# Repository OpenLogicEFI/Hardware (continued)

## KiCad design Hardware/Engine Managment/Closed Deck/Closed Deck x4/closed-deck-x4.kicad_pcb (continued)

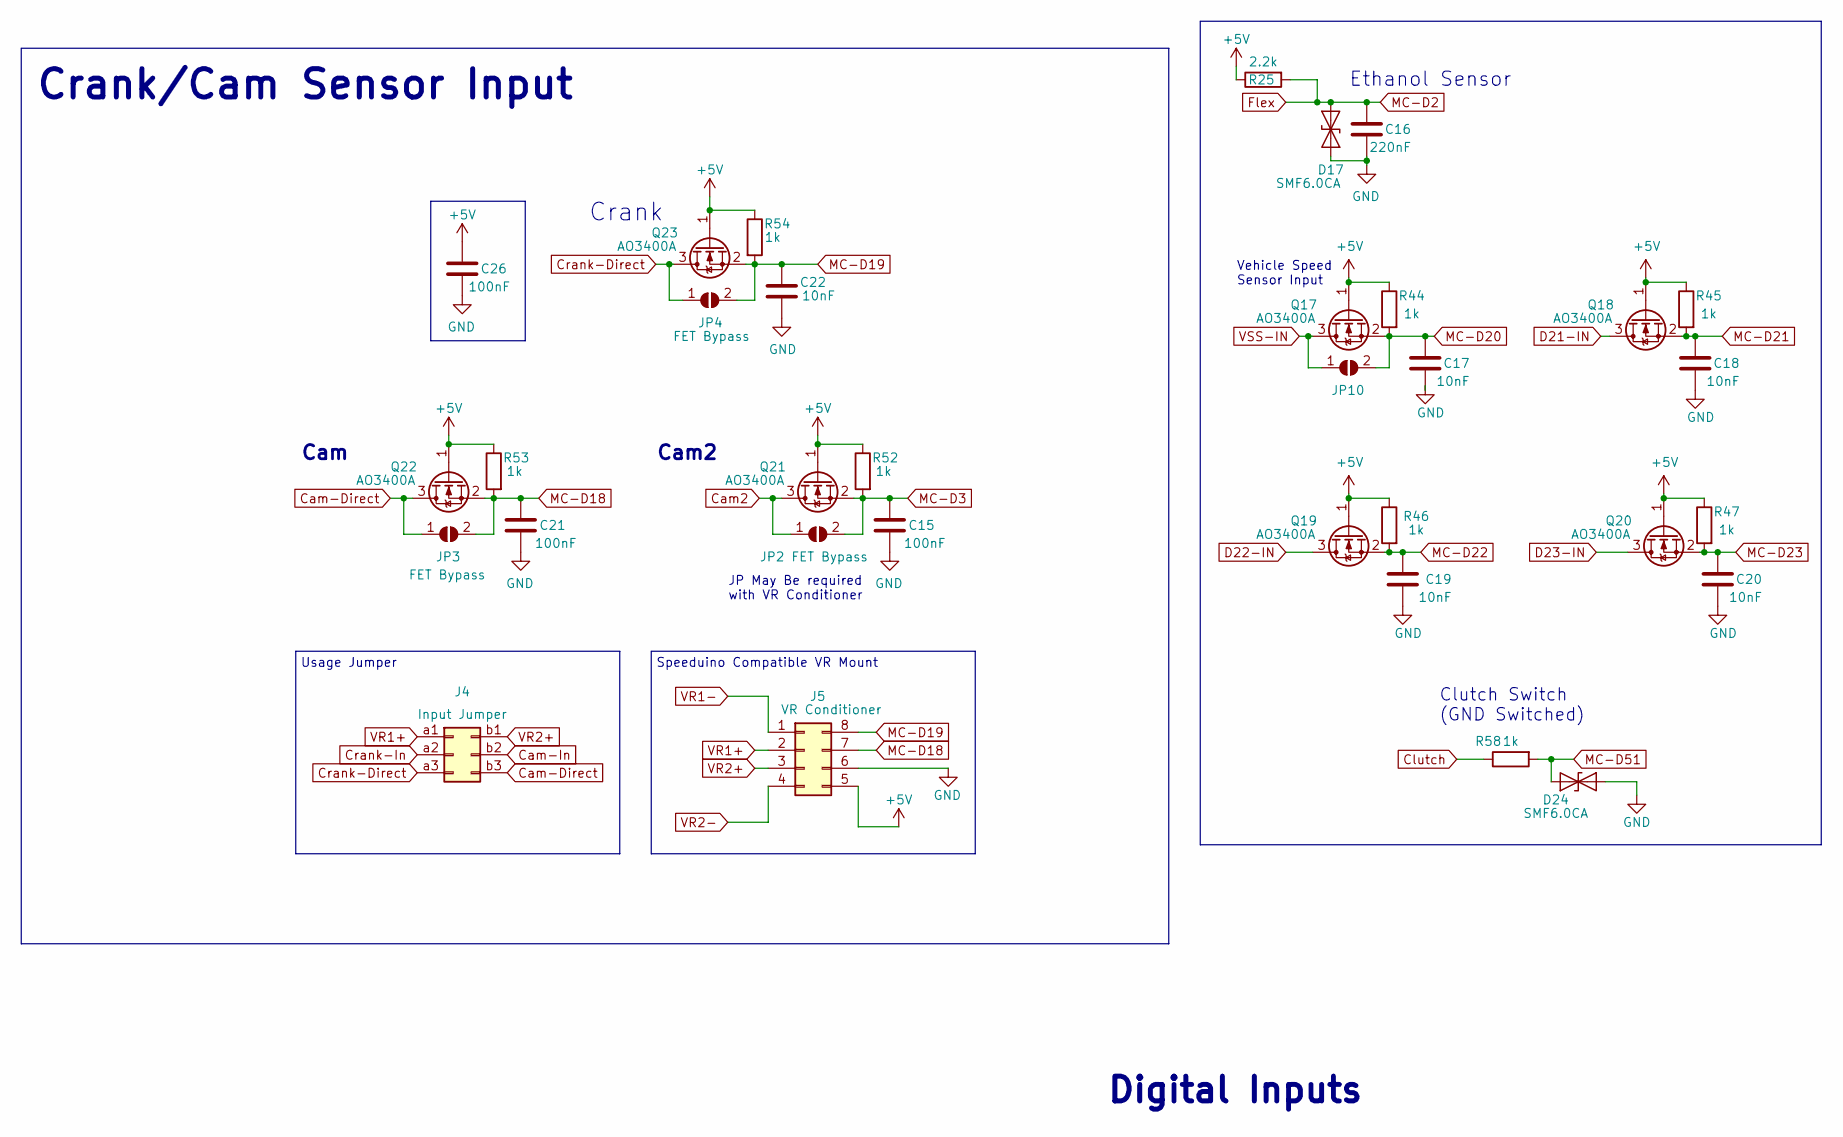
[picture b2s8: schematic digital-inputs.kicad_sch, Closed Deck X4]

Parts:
C15, C21, C26: 100nF; C_0402_1005Metric; LCSC C307331
C16: 220nF; C_0402_1005Metric; LCSC C16772
C17, C18, C19, C20, C22: 10nF; C_0402_1005Metric; LCSC C15195
D17, D24: SMF6.0CA; D_SOD-123F; LCSC C2990473
J4: Input Jumper; PinHeader2x03_Jumper
J5: VR Conditioner; Socket_VRConditioner_Corrected
JP2, JP3, JP4, JP10: FET Bypass; SolderJumper-2_P1.3mm_Open_RoundedPad1.0x1.5mm
Q17, Q18, Q19, Q20, Q21, Q22, Q23: AO3400A; SOT-23
R25: 2.2k; R_0402_1005Metric; Manufacture Part Number 0402WGF2201TCE; LCSC C25879
R44, R45, R46, R47, R52, R53, R54, R58: 1k; R_0402_1005Metric; Manufacture Part Number 0402WGF1001TCE; LCSC C11702

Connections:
+5V: C26.2, J5.5, Q17.1 (G), Q18.1 (G), Q19.1 (G), Q20.1 (G), Q21.1 (G), Q22.1 (G), Q23.1 (G), R25.1, R44.1, R45.1, R46.1, R47.1, R52.1, R53.1, R54.1; also elsewhere on the board
Cam2: JP2.1 (A), Q21.3 (D); also elsewhere on the board
Cam-Direct: J4.b3, JP3.1 (A), Q22.3 (D)
Cam-In: J4.b2; also elsewhere on the board
Clutch: R58.1; also elsewhere on the board
Crank-Direct: J4.a3, JP4.1 (A), Q23.3 (D)
Crank-In: J4.a2; also elsewhere on the board
D21-IN: Q18.3 (D); also elsewhere on the board
D22-IN: Q19.3 (D); also elsewhere on the board
D23-IN: Q20.3 (D); also elsewhere on the board
Flex: C16.1, D17.1 (A1), R25.2; also elsewhere on the board
GND: C15.1, C16.2, C17.2, C18.2, C19.2, C20.2, C21.1, C22.1, C26.1, D17.2 (A2), D24.1 (A1), J5.6; also elsewhere on the board
MC-D3: C15.2, JP2.2 (B), Q21.2 (S), R52.2; also elsewhere on the board
MC-D18: C21.2, J5.7, JP3.2 (B), Q22.2 (S), R53.2; also elsewhere on the board
MC-D19: C22.2, J5.8, JP4.2 (B), Q23.2 (S), R54.2; also elsewhere on the board
MC-D20: C17.1, JP10.2 (B), Q17.2 (S), R44.2; also elsewhere on the board
MC-D21: C18.1, Q18.2 (S), R45.2; also elsewhere on the board
MC-D22: C19.1, Q19.2 (S), R46.2; also elsewhere on the board
MC-D23: C20.1, Q20.2 (S), R47.2; also elsewhere on the board
MC-D51: D24.2 (A2), R58.2; also elsewhere on the board
VR1+: J4.a1, J5.2
VR1-: J5.1; also elsewhere on the board
VR2+: J4.b1, J5.3
VR2-: J5.4; also elsewhere on the board
VSS-IN: JP10.1 (A), Q17.3 (D); also elsewhere on the board

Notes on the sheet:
Vehicle Speed Sensor Input
JP May Be required with VR Conditioner
Cam
Speeduino Compatible VR Mount
Clutch Switch (GND Switched)
Ethanol Sensor
Usage Jumper
Crank
Crank/Cam Sensor Input
Cam2
Digital Inputs

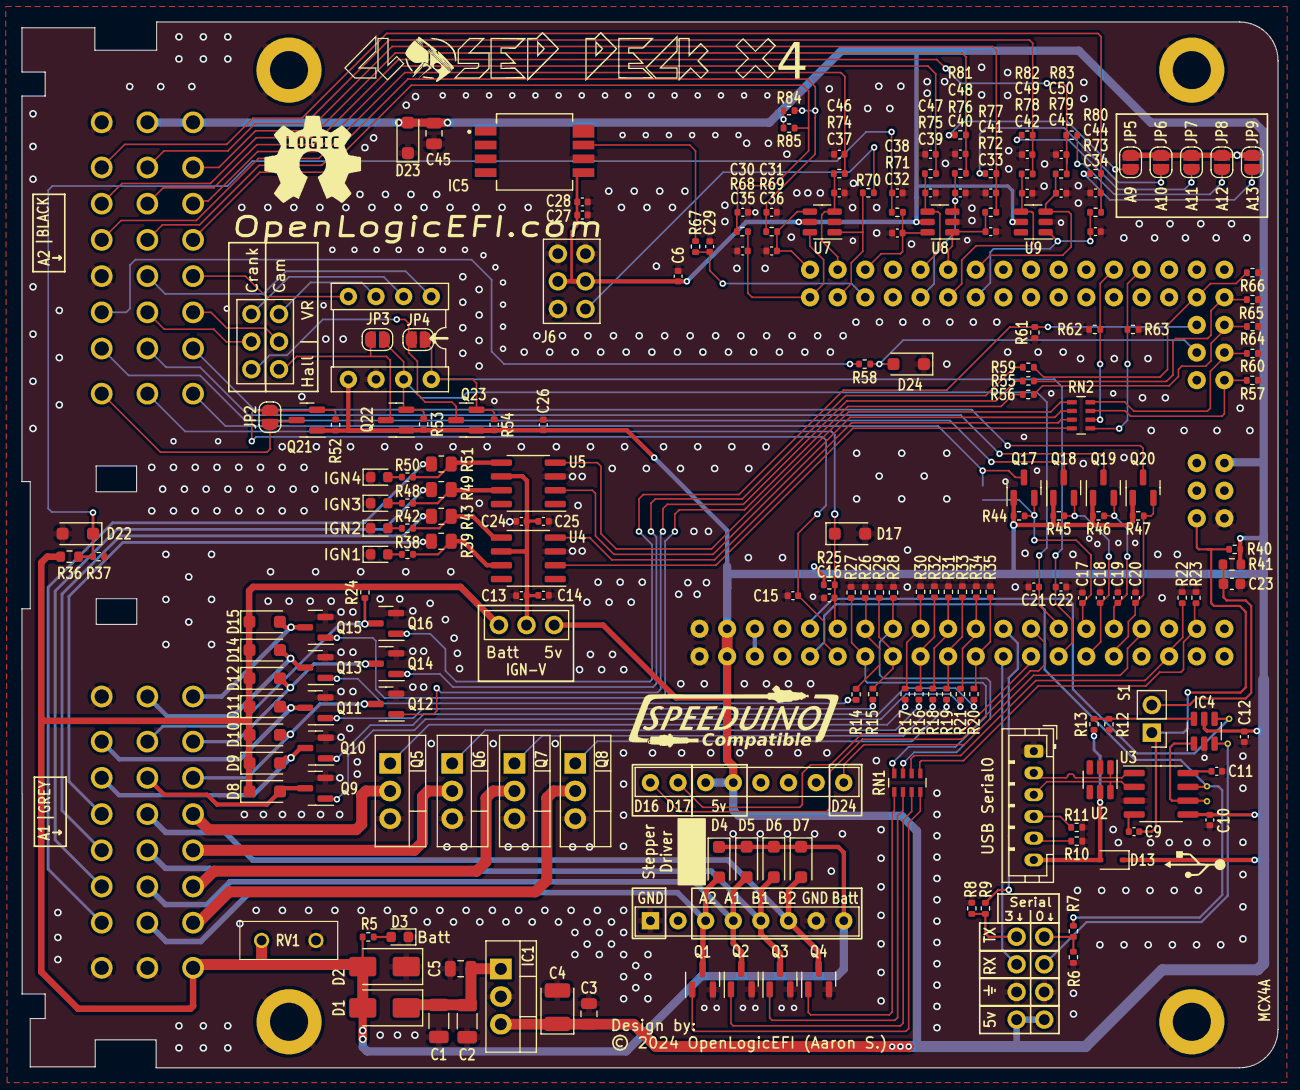
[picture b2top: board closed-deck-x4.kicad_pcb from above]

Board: 2 copper layers, 115.5 x 96.2 mm, 216 parts (1 on the bottom side), 147 nets.

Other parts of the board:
U6: MEGA_PRO_EMBED_CH340G_{slash}_ATMEGA2560; Arduino_Mega_Mini_2560_SmallCrtYd_NoVin

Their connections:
+3.3V: U6.3V3_1 (3V3), U6.3V3_2 (3V3)
+5V: U6.5V_1 (5V), U6.5V_2 (5V), U6.5V_3 (5V); also elsewhere on the board
Flex: U6.D2; also elsewhere on the board
GND: U6.GND_1 (GND), U6.GND_2 (GND), U6.GND_3 (GND); also elsewhere on the board
MC-A0: U6.A0; also elsewhere on the board
MC-A1: U6.A1; also elsewhere on the board
MC-A2: U6.A2; also elsewhere on the board
MC-A3: U6.A3; also elsewhere on the board
MC-A4: U6.A4; also elsewhere on the board
MC-A5: U6.A5; also elsewhere on the board
MC-A8: U6.A8; also elsewhere on the board
MC-A9: U6.A9; also elsewhere on the board
MC-A10: U6.A10; also elsewhere on the board
MC-A11: U6.A11; also elsewhere on the board
MC-A12: U6.A12; also elsewhere on the board
MC-A13: U6.A13; also elsewhere on the board
MC-D0-RX0: U6.RX; also elsewhere on the board
MC-D1-TX0: U6.TX; also elsewhere on the board
MC-D3: U6.D3; also elsewhere on the board
MC-D4: U6.D4; also elsewhere on the board
MC-D5: U6.D5; also elsewhere on the board
MC-D6: U6.D6; also elsewhere on the board
MC-D7: U6.D7; also elsewhere on the board
MC-D8: U6.D8; also elsewhere on the board
MC-D9: U6.D9; also elsewhere on the board
MC-D10: U6.D10; also elsewhere on the board
MC-D11: U6.D11; also elsewhere on the board
MC-D12: U6.D12; also elsewhere on the board
MC-D13: U6.D13; also elsewhere on the board
MC-D14-TX3: U6.D14; also elsewhere on the board
MC-D15-RX3: U6.D15; also elsewhere on the board
MC-D16: U6.D16; also elsewhere on the board
MC-D17: U6.D17; also elsewhere on the board
MC-D18: U6.D18; also elsewhere on the board
MC-D19: U6.D19; also elsewhere on the board
MC-D20: U6.D20; also elsewhere on the board
MC-D21: U6.D21; also elsewhere on the board
MC-D22: U6.D22; also elsewhere on the board
MC-D23: U6.D23; also elsewhere on the board
MC-D24: U6.D24; also elsewhere on the board
MC-D27: U6.D27; also elsewhere on the board
MC-D28: U6.D28; also elsewhere on the board
MC-D38: U6.D38; also elsewhere on the board
MC-D40: U6.D40; also elsewhere on the board
MC-D45: U6.D45; also elsewhere on the board
MC-D47: U6.D47; also elsewhere on the board
MC-D48: U6.D48; also elsewhere on the board
MC-D49: U6.D49; also elsewhere on the board
MC-D50: U6.D50; also elsewhere on the board
MC-D51: U6.D51; also elsewhere on the board
MC-D52: U6.D52; also elsewhere on the board
MC-RESET: U6.RESET; also elsewhere on the board

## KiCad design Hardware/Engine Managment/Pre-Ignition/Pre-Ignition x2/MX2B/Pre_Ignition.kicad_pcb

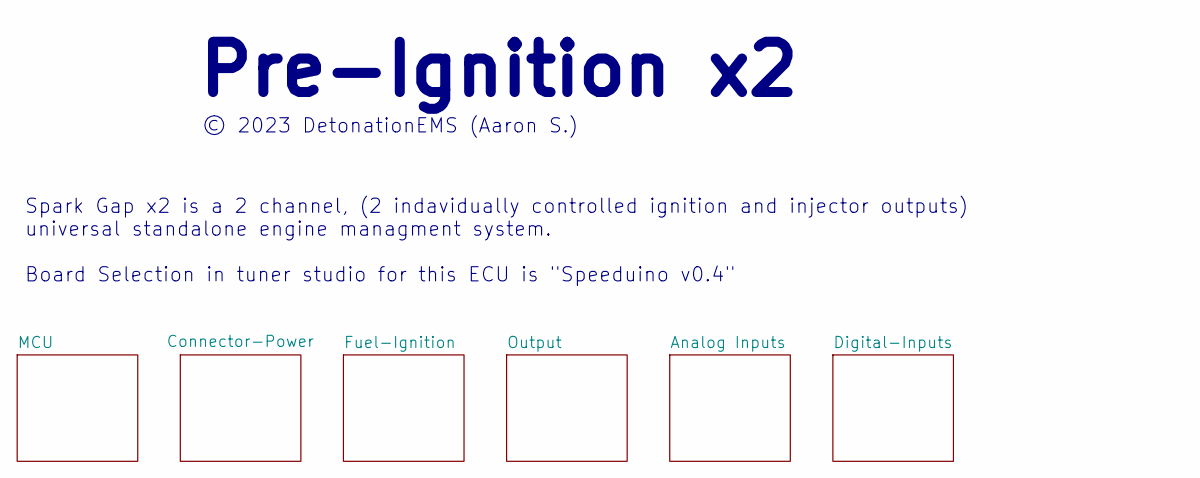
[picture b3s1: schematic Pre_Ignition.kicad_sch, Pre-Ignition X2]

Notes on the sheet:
Pre-Ignition x2
Spark Gap x2 is a 2 channel, (2 indavidually controlled ignition and injector outputs) universal standalone engine managment system. Board Selection in tuner studio for this ECU is "Speeduino v0.4"
© 2023 DetonationEMS (Aaron S.)

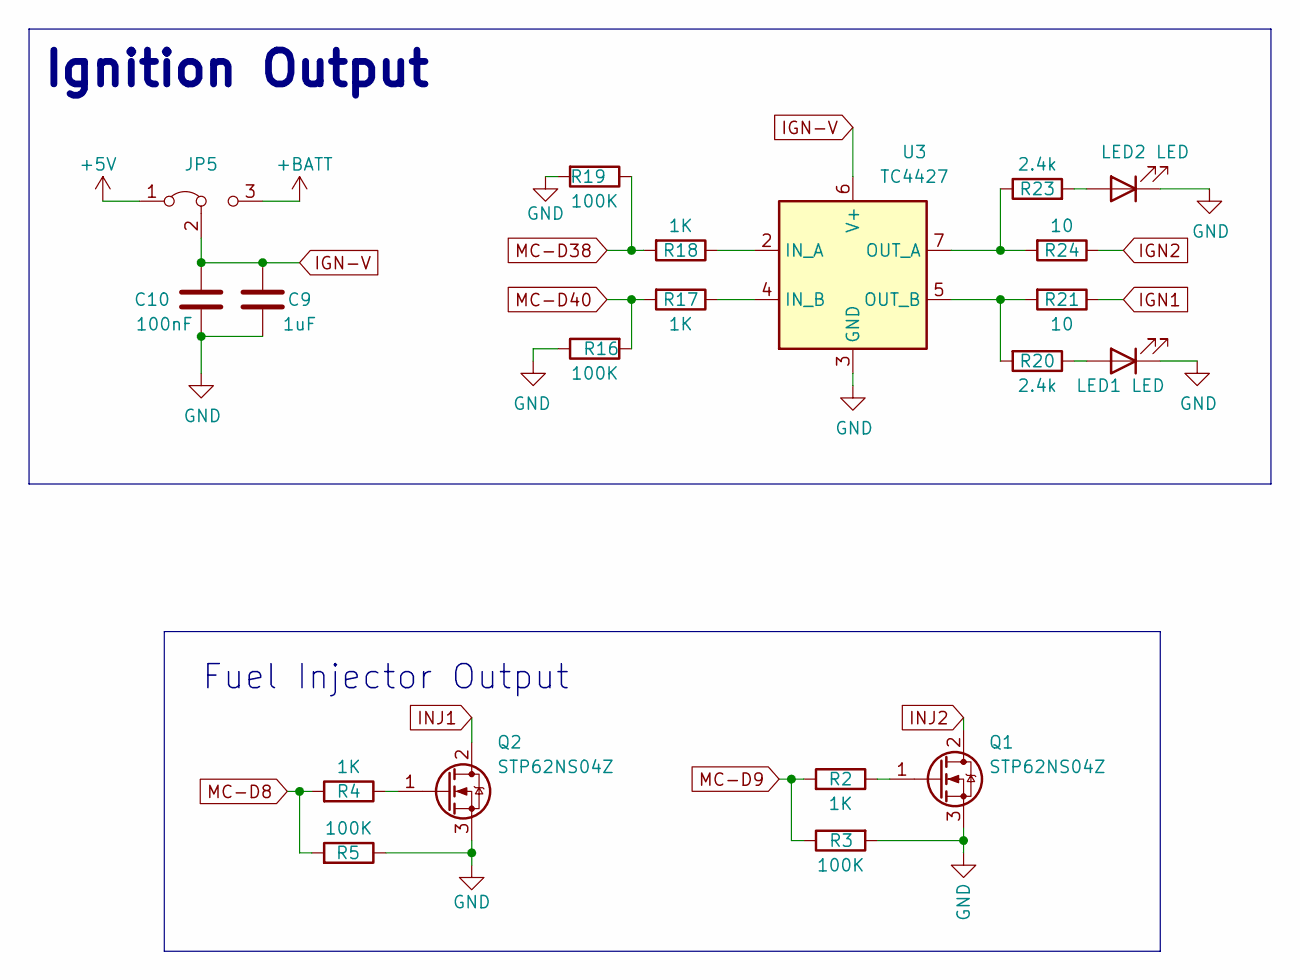
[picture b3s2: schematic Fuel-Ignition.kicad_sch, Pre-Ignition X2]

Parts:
C9: 1uF; C_0603_1608Metric; LCSC C15849
C10: 100nF; C_0603_1608Metric; LCSC C14663
JP5: Jumper_3_Bridged12; SolderJumper-3_P1.3mm_Bridged12_RoundedPad1.0x1.5mm_NumberL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
LED1, LED2: LED; LED_0603_1608Metric; LCSC C2286
Q1: STP62NS04Z; TO-220-3_Vertical; Manufacturer_Part_Number STP62NS04Z; Mouser Part Number 511-STP62NS04Z
Q2: STP62NS04Z; TO-220-3_Vertical; Manufacturer_Part_Number STP62NS04Z
R2, R4, R17, R18: 1K; R_0603_1608Metric; LCSC C21190
R3, R5, R16, R19: 100K; R_0603_1608Metric; LCSC C25803
R20, R23: 2.4k; R_0603_1608Metric; LCSC C22940
R21, R24: 10; R_1206_3216Metric; LCSC C17903
U3: TC4427; SOIC-8_3.9x4.9mm_P1.27mm; LCSC C31450

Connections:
+BATT: JP5.3 (B); also elsewhere on the board
IGN1: R21.1; also elsewhere on the board
IGN2: R24.1; also elsewhere on the board
IGN-V: C9.1, C10.1, JP5.2 (C), U3.6 (V+)
INJ1: Q2.2 (D); also elsewhere on the board
INJ2: Q1.2 (D); also elsewhere on the board
MC-D8: R4.2, R5.2; also elsewhere on the board
MC-D9: R2.2, R3.1; also elsewhere on the board
MC-D38: R18.2, R19.1; also elsewhere on the board
MC-D40: R16.2, R17.2; also elsewhere on the board
unnamed: LED1.2 (A), R20.1
unnamed: LED2.2 (A), R23.2
unnamed: Q1.1 (G), R2.1
unnamed: Q2.1 (G), R4.1
unnamed: R18.1, U3.2 (IN_A)
unnamed: R17.1, U3.4 (IN_B)
unnamed: R23.1, R24.2, U3.7 (OUT_A)
unnamed: R20.2, R21.2, U3.5 (OUT_B)

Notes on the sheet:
Ignition Output
Fuel Injector Output

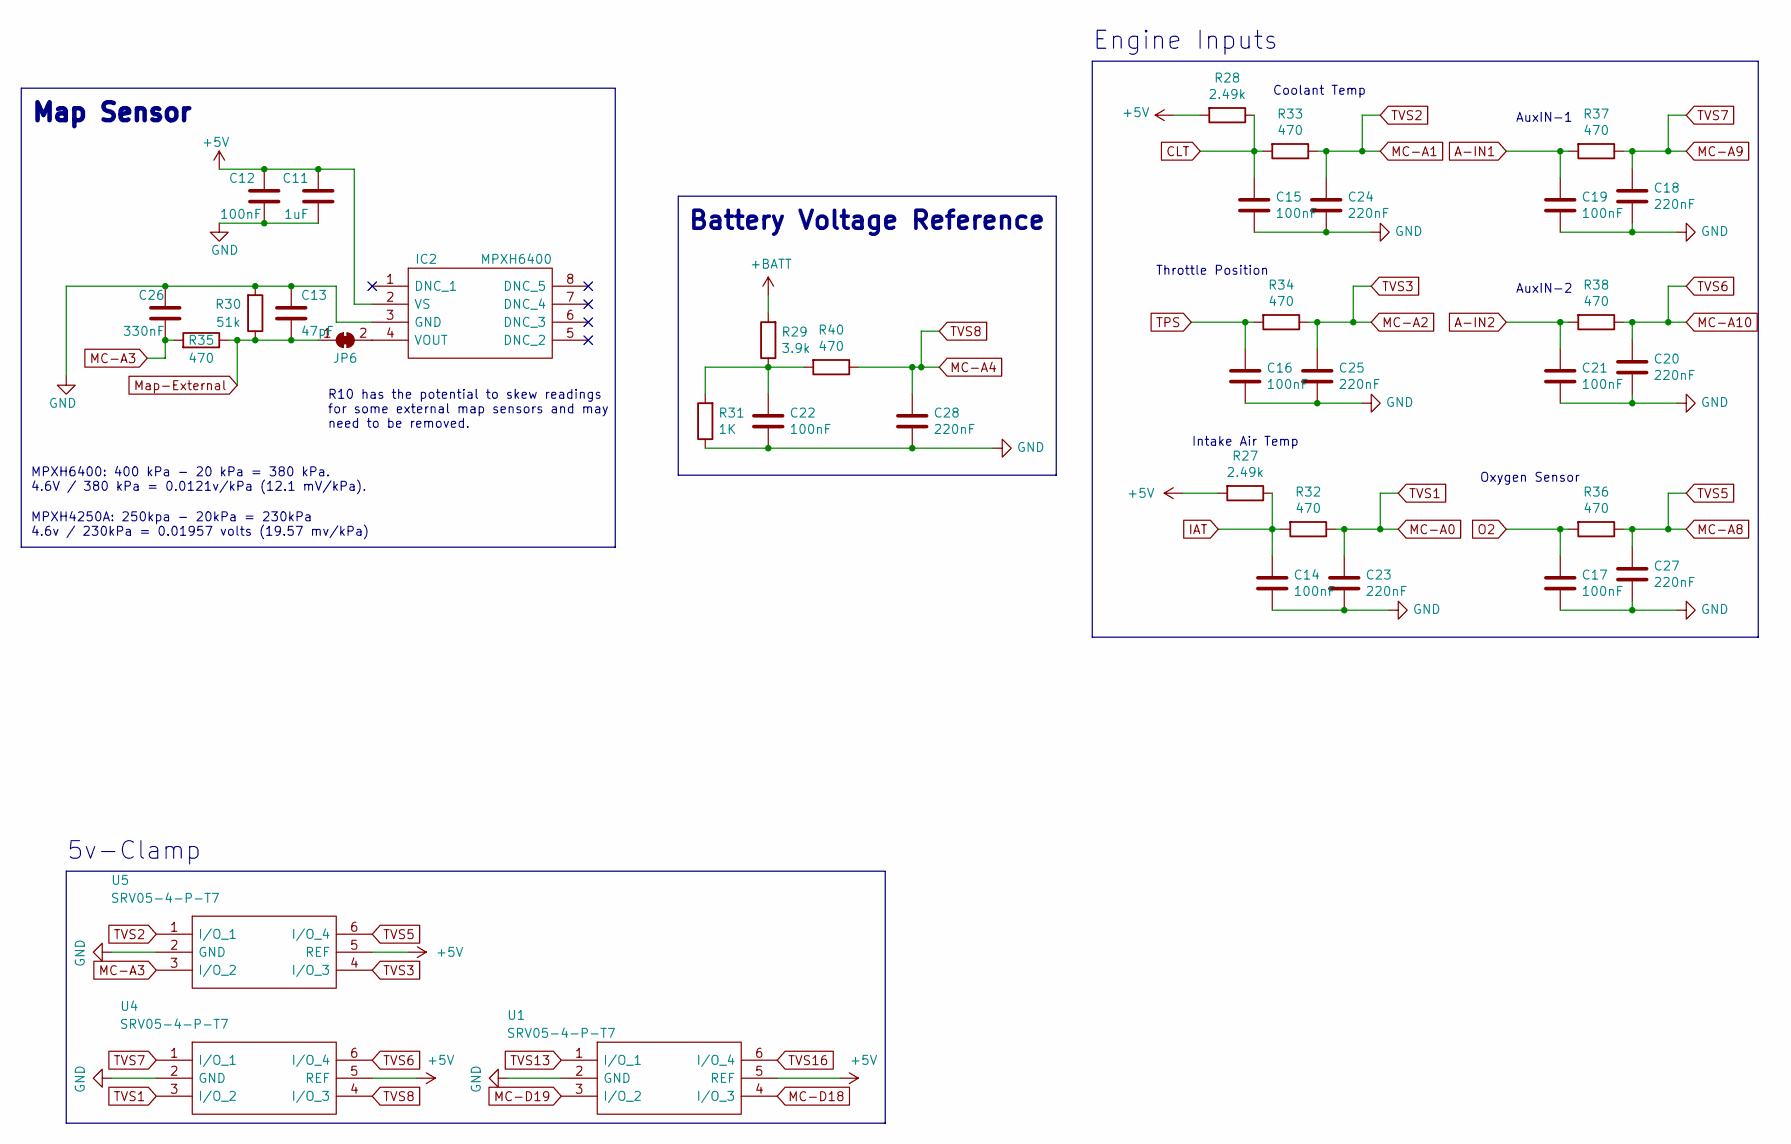
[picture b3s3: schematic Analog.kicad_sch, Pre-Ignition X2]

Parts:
C11: 1uF; C_0603_1608Metric; LCSC C15849
C12, C14, C15, C16, C17, C19, C21, C22: 100nF; C_0603_1608Metric; LCSC C14663
C13: 47pF; C_0603_1608Metric; LCSC C1671
C18, C20, C23, C24, C25, C27, C28: 220nF; C_0603_1608Metric; LCSC C5378
C26: 330nF; C_0603_1608Metric; LCSC C1615
IC2: MPXH6400; MPXH6250; Manufacturer_Part_Number MPXH6250AC6U; Mouser Part Number 841-MPXH6250AC6U
JP6: SolderJumper-2_P1.3mm_Bridged_RoundedPad1.0x1.5mm
R27, R28: 2.49k; R_0603_1608Metric; LCSC C309658
R29: 3.9k; R_0603_1608Metric; LCSC C23018
R30: 51k; R_0603_1608Metric; LCSC C23196
R31: 1K; R_0603_1608Metric; LCSC C21190
R32, R33, R34, R35, R36, R37, R38, R40: 470; R_0603_1608Metric; LCSC C23179
U1, U4, U5: SRV05-4-P-T7; SOT-23-6; LCSC C85364

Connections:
+BATT: R29.2; also elsewhere on the board
A-IN1: C19.1, R37.2; also elsewhere on the board
A-IN2: C21.1, R38.2; also elsewhere on the board
CLT: C15.1, R28.1, R33.2; also elsewhere on the board
IAT: C14.1, R27.1, R32.2; also elsewhere on the board
MC-A0: C23.1, R32.1, U4.3 (I/O_2); also elsewhere on the board
MC-A1: C24.1, R33.1, U5.1 (I/O_1); also elsewhere on the board
MC-A3: C26.2, R35.2, U5.3 (I/O_2); also elsewhere on the board
MC-A4: C28.1, R40.1, U4.4 (I/O_3); also elsewhere on the board
MC-A8: C27.1, R36.1, U5.6 (I/O_4); also elsewhere on the board
MC-A9: C18.1, R37.1, U4.1 (I/O_1); also elsewhere on the board
MC-A10: C20.1, R38.1, U4.6 (I/O_4); also elsewhere on the board
MC-D18: U1.4 (I/O_3); also elsewhere on the board
Map-External: C13.1, JP6.1 (A), R30.1, R35.1; also elsewhere on the board
unnamed: C22.1, R29.1, R31.2, R40.2
unnamed: IC2.4 (VOUT), JP6.2 (B)
O2: C17.1, R36.2; also elsewhere on the board
TPS: C16.1, R34.2; also elsewhere on the board
TVS13: U1.1 (I/O_1)
TVS16: U1.6 (I/O_4)

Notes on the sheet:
R10 has the potential to skew readings for some external map sensors and may need to be removed.
5v-Clamp
Coolant Temp
Oxygen Sensor
Engine Inputs
AuxIN-2
Battery Voltage Reference
Map Sensor
MPXH4250A: 250kpa - 20kPa = 230kPa 4.6v / 230kPa = 0.01957 volts (19.57 mv/kPa)
MPXH6400: 400 kPa - 20 kPa = 380 kPa. 4.6V / 380 kPa = 0.0121v/kPa (12.1 mV/kPa).
Intake Air Temp
Throttle Position
AuxIN-1

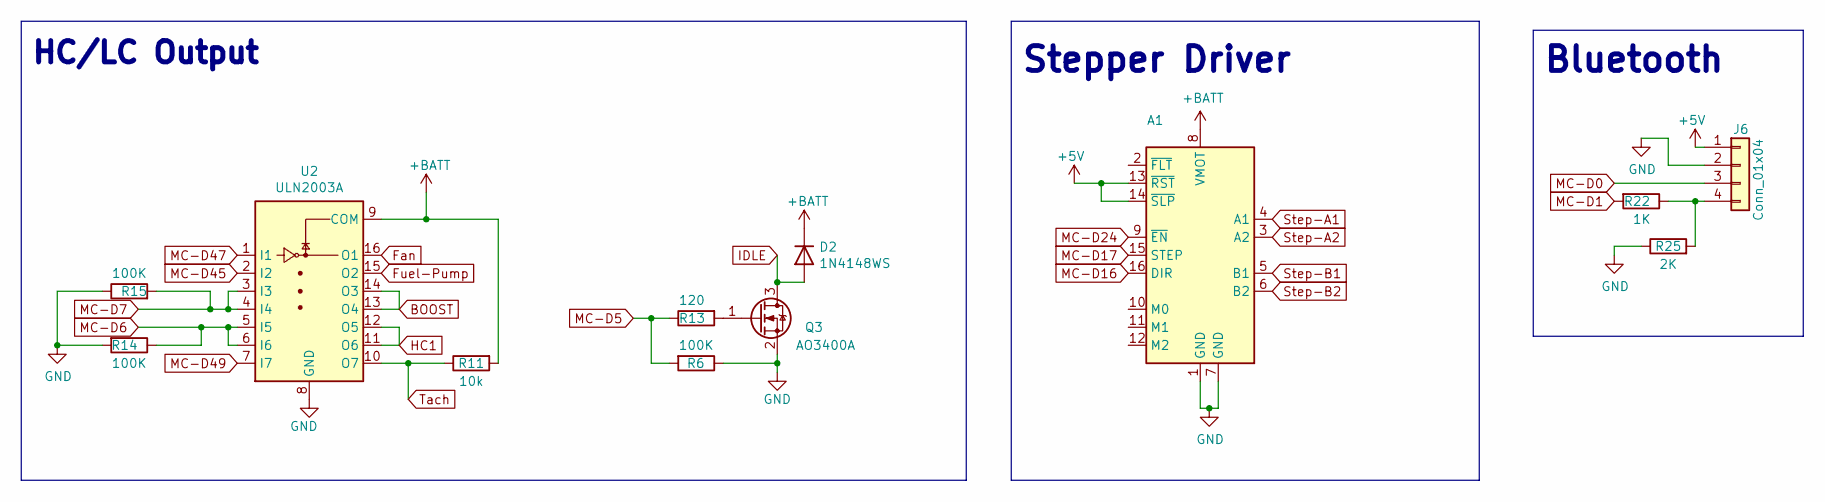
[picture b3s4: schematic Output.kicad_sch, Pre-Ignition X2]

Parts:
A1: Pololu_Breakout_DRV8825; DVR8825-Labeled-Front
D2: 1N4148WS; D_SOD-323F; LCSC C2128
J6: Conn_01x04; 1X4-PROTO
Q3: AO3400A; SOT-23; LCSC C20917
R6, R14, R15: 100K; R_0603_1608Metric; LCSC C25803
R11: 10k; R_0603_1608Metric; LCSC C25804
R13: 120; R_0603_1608Metric; LCSC C22787
R22: 1K; R_0603_1608Metric; LCSC C21190
R25: 2K; R_0603_1608Metric; LCSC C22975
U2: ULN2003A; SOIC-16_3.9x9.9mm_P1.27mm; LCSC C7512

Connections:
+BATT: A1.8 (VMOT), D2.1 (K), R11.2, U2.9 (COM); also elsewhere on the board
BOOST: U2.13 (O4), U2.14 (O3); also elsewhere on the board
Fan: U2.16 (O1); also elsewhere on the board
Fuel-Pump: U2.15 (O2); also elsewhere on the board
HC1: U2.11 (O6), U2.12 (O5); also elsewhere on the board
IDLE: D2.2 (A), Q3.3 (D); also elsewhere on the board
MC-D0: J6.3; also elsewhere on the board
MC-D1: R22.2; also elsewhere on the board
MC-D5: R6.2, R13.1; also elsewhere on the board
MC-D6: R14.1, U2.5 (I5), U2.6 (I6); also elsewhere on the board
MC-D7: R15.2, U2.3 (I3), U2.4 (I4); also elsewhere on the board
MC-D16: A1.16 (DIR); also elsewhere on the board
MC-D17: A1.15 (STEP); also elsewhere on the board
MC-D24: A1.9 (~EN); also elsewhere on the board
MC-D45: U2.2 (I2); also elsewhere on the board
MC-D47: U2.1 (I1); also elsewhere on the board
MC-D49: U2.7 (I7); also elsewhere on the board
unnamed: J6.4, R22.1, R25.2
unnamed: Q3.1 (G), R13.2
Step-A1: A1.4 (A1); also elsewhere on the board
Step-A2: A1.3 (A2); also elsewhere on the board
Step-B1: A1.5 (B1); also elsewhere on the board
Step-B2: A1.6 (B2); also elsewhere on the board
Tach: R11.1, U2.10 (O7); also elsewhere on the board

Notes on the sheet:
Bluetooth
Stepper Driver
HC/LC Output

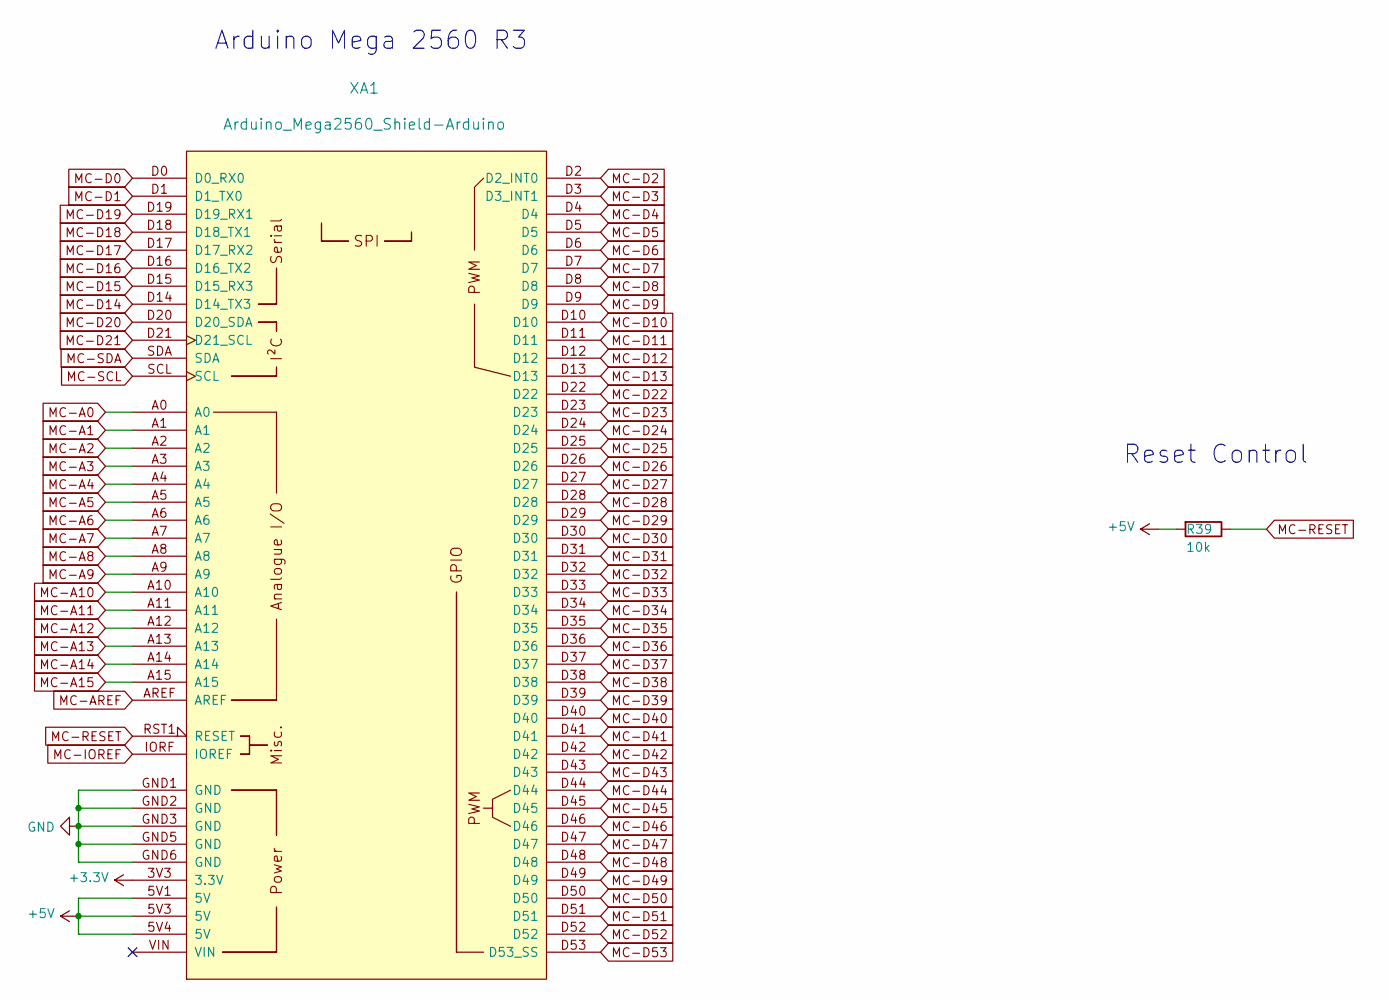
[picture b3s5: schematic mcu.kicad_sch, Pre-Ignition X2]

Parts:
R39: 10k; R_0603_1608Metric; LCSC C25804
XA1: Arduino_Mega2560_Shield-Arduino; Arduino_Mega2560_Shield_IO_Only_No_Silk_Screen

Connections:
+3V3: XA1.3V3 (3.3V)
Flex: XA1.D2 (D2_INT0); also elsewhere on the board
MC-A0: XA1.A0; also elsewhere on the board
MC-A1: XA1.A1; also elsewhere on the board
MC-A3: XA1.A3; also elsewhere on the board
MC-A4: XA1.A4; also elsewhere on the board
MC-A5: XA1.A5
MC-A6: XA1.A6
MC-A7: XA1.A7
MC-A8: XA1.A8; also elsewhere on the board
MC-A9: XA1.A9; also elsewhere on the board
MC-A10: XA1.A10; also elsewhere on the board
MC-A11: XA1.A11
MC-A12: XA1.A12
MC-A13: XA1.A13
MC-A14: XA1.A14
MC-A15: XA1.A15
MC-AREF: XA1.AREF
MC-D0: XA1.D0 (D0_RX0); also elsewhere on the board
MC-D1: XA1.D1 (D1_TX0); also elsewhere on the board
MC-D3: XA1.D3 (D3_INT1)
MC-D4: XA1.D4
MC-D5: XA1.D5; also elsewhere on the board
MC-D6: XA1.D6; also elsewhere on the board
MC-D7: XA1.D7; also elsewhere on the board
MC-D8: XA1.D8; also elsewhere on the board
MC-D9: XA1.D9; also elsewhere on the board
MC-D10: XA1.D10
MC-D11: XA1.D11
MC-D12: XA1.D12
MC-D13: XA1.D13
MC-D14: XA1.D14 (D14_TX3)
MC-D15: XA1.D15 (D15_RX3)
MC-D16: XA1.D16 (D16_TX2); also elsewhere on the board
MC-D17: XA1.D17 (D17_RX2); also elsewhere on the board
MC-D18: XA1.D18 (D18_TX1); also elsewhere on the board
MC-D20: XA1.D20 (D20_SDA); also elsewhere on the board
MC-D21: XA1.D21 (D21_SCL)
MC-D22: XA1.D22
MC-D23: XA1.D23
MC-D24: XA1.D24; also elsewhere on the board
MC-D25: XA1.D25
MC-D26: XA1.D26
MC-D27: XA1.D27
MC-D28: XA1.D28
MC-D29: XA1.D29
MC-D30: XA1.D30
MC-D31: XA1.D31
MC-D32: XA1.D32
MC-D33: XA1.D33
MC-D34: XA1.D34
MC-D35: XA1.D35
MC-D36: XA1.D36
MC-D37: XA1.D37
MC-D38: XA1.D38; also elsewhere on the board
MC-D39: XA1.D39
MC-D40: XA1.D40; also elsewhere on the board
MC-D41: XA1.D41
MC-D42: XA1.D42
MC-D43: XA1.D43
MC-D44: XA1.D44
MC-D45: XA1.D45; also elsewhere on the board
MC-D46: XA1.D46
MC-D47: XA1.D47; also elsewhere on the board
MC-D48: XA1.D48
MC-D49: XA1.D49; also elsewhere on the board
MC-D50: XA1.D50
MC-D51: XA1.D51; also elsewhere on the board
MC-D52: XA1.D52
MC-D53: XA1.D53 (D53_SS)
MC-IOREF: XA1.IORF (IOREF)
MC-RESET: R39.1, XA1.RST1 (RESET)
MC-SCL: XA1.SCL
MC-SDA: XA1.SDA

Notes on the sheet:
Arduino Mega 2560 R3
Reset Control

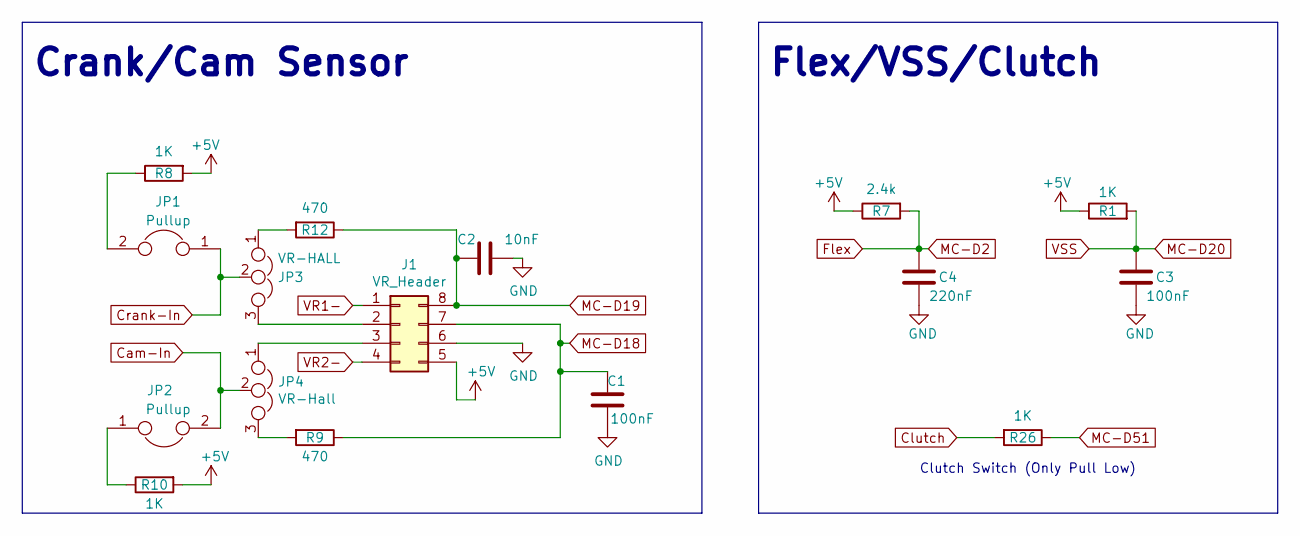
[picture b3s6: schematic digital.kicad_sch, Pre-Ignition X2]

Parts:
C1, C3: 100nF; C_0603_1608Metric; LCSC C14663
C2: 10nF; C_0603_1608Metric; LCSC C57112
C4: 220nF; C_0603_1608Metric; LCSC C5378
J1: VR_Header; DIP-8_W7.62mm_Socket_VRConditioner
JP1, JP2: Pullup; 1x02-Proto
JP3: VR-HALL; 3x1-GPIO
JP4: VR-Hall; 3x1-GPIO
R1, R8, R10, R26: 1K; R_0603_1608Metric; LCSC C21190
R7: 2.4k; R_0603_1608Metric; LCSC C22940
R9, R12: 470; R_0603_1608Metric; LCSC C23179

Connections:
Cam-In: JP2.2, JP4.2; also elsewhere on the board
Clutch: R26.2; also elsewhere on the board
Crank-In: JP1.1, JP3.2; also elsewhere on the board
Flex: C4.1, R7.2; also elsewhere on the board
MC-D18: C1.2, J1.7, R9.1; also elsewhere on the board
MC-D20: C3.1, R1.2; also elsewhere on the board
MC-D51: R26.1; also elsewhere on the board
unnamed: J1.2, JP3.3
unnamed: J1.3, JP4.1
unnamed: JP1.2, R8.1
unnamed: JP2.1, R10.1
unnamed: JP3.1, R12.2
unnamed: JP4.3, R9.2
VR1-: J1.1; also elsewhere on the board
VR2-: J1.4; also elsewhere on the board

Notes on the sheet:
Crank/Cam Sensor
Clutch Switch (Only Pull Low)
Flex/VSS/Clutch

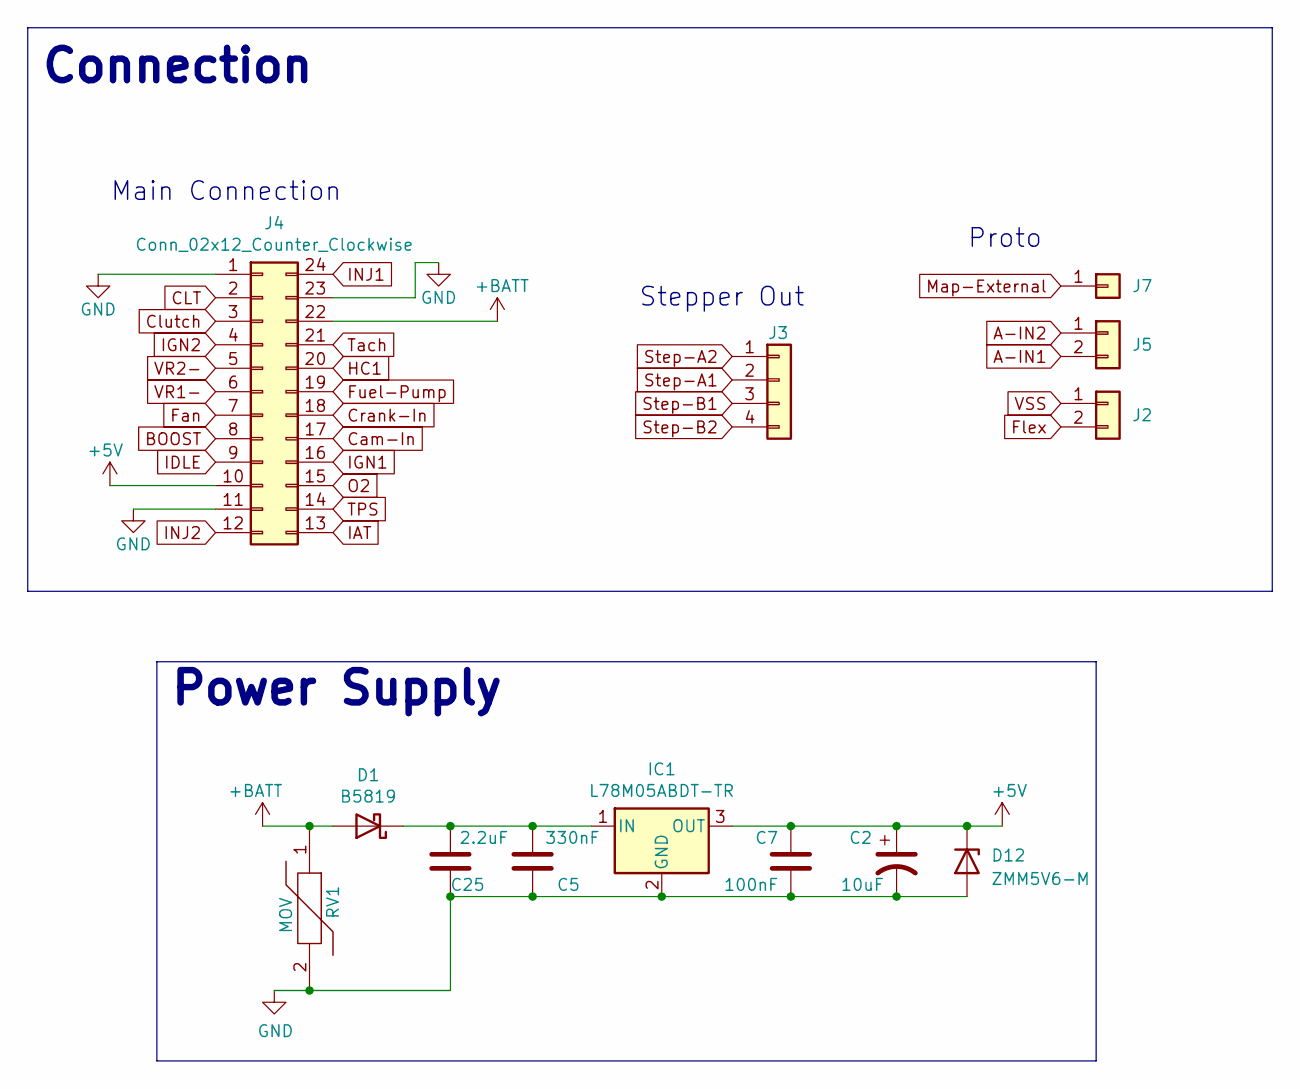
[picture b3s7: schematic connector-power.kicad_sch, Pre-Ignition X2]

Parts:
C2: 10uF; CP_EIA-3216-18_Kemet-A; Manufacture Part Number TAJA106K016RNJ; LCSC C7171
C5: 330nF; C_0603_1608Metric; LCSC C1615
C7: 100nF; C_0603_1608Metric; LCSC C14663
C25: 2.2uF; C_1206_3216Metric; Manufacture Part Number CL31B225KBHNNNE; LCSC C50254
D1: B5819; D_SOD-123; LCSC C8598
D12: ZMM5V6-M; D_MiniMELF; LCSC C8062
IC1: L78M05ABDT-TR; TO-252-2-Thermal; Manufacturer_Part_Number L78M05ABDT-TR; LCSC C58069
J2, J5: Conn_01x04; 1x02-Proto
J3: Conn_01x04; 1X4-PROTO
J4: Conn_02x12_Counter_Clockwise; Molex_Micro-Fit_3.0_43045-2400_2x12_P3.00mm_Horizontal
J7: Conn_01x04; 1x1-GPIO
RV1: MOV; MOV07D220KTR; Manufacturer_Part_Number MOV-14D220K; Mouser Part Number 652-MOV-14D220K

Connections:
+BATT: D1.2 (A), J4.22, RV1.1; also elsewhere on the board
A-IN1: J5.2; also elsewhere on the board
A-IN2: J5.1; also elsewhere on the board
BOOST: J4.8; also elsewhere on the board
CLT: J4.2; also elsewhere on the board
Cam-In: J4.17; also elsewhere on the board
Clutch: J4.3; also elsewhere on the board
Crank-In: J4.18; also elsewhere on the board
Fan: J4.7; also elsewhere on the board
Flex: J2.2; also elsewhere on the board
Fuel-Pump: J4.19; also elsewhere on the board
HC1: J4.20; also elsewhere on the board
IAT: J4.13; also elsewhere on the board
IDLE: J4.9; also elsewhere on the board
IGN1: J4.16; also elsewhere on the board
IGN2: J4.4; also elsewhere on the board
INJ1: J4.24; also elsewhere on the board
INJ2: J4.12; also elsewhere on the board
MC-D20: J2.1; also elsewhere on the board
Map-External: J7.1; also elsewhere on the board
O2: J4.15; also elsewhere on the board
Step-A1: J3.2; also elsewhere on the board
Step-A2: J3.1; also elsewhere on the board
Step-B1: J3.3; also elsewhere on the board
Step-B2: J3.4; also elsewhere on the board
TPS: J4.14; also elsewhere on the board
Tach: J4.21; also elsewhere on the board
VR1-: J4.6; also elsewhere on the board
VR2-: J4.5; also elsewhere on the board

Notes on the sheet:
Main Connection
Connection
Power Supply
Proto
Stepper Out

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
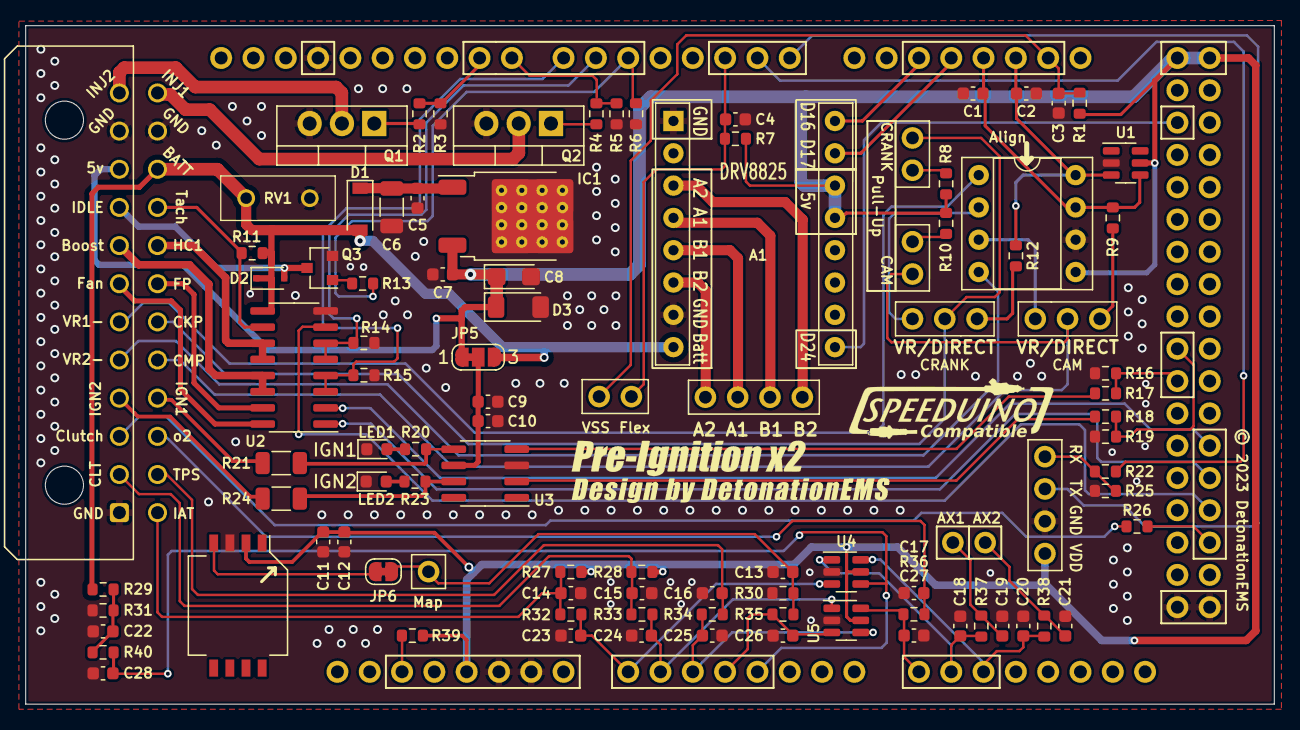
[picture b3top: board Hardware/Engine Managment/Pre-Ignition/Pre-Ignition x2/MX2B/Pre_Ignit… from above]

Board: 2 copper layers, 98.2 x 53.3 mm, 102 parts (0 on the bottom side), 78 nets.

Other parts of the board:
C6: 330nF; C_1206_3216Metric
C8: 10uF; CP_EIA-3216-18_Kemet-A
D3: ZMM5V6-M; D_MiniMELF
G1: Logo_Open_Hardware_Small; SpeeduinoCompatible-17mm
G2: Logo_Open_Hardware_Small; Pre-Ignition-800
G3: LOGO; Design by 25mm
